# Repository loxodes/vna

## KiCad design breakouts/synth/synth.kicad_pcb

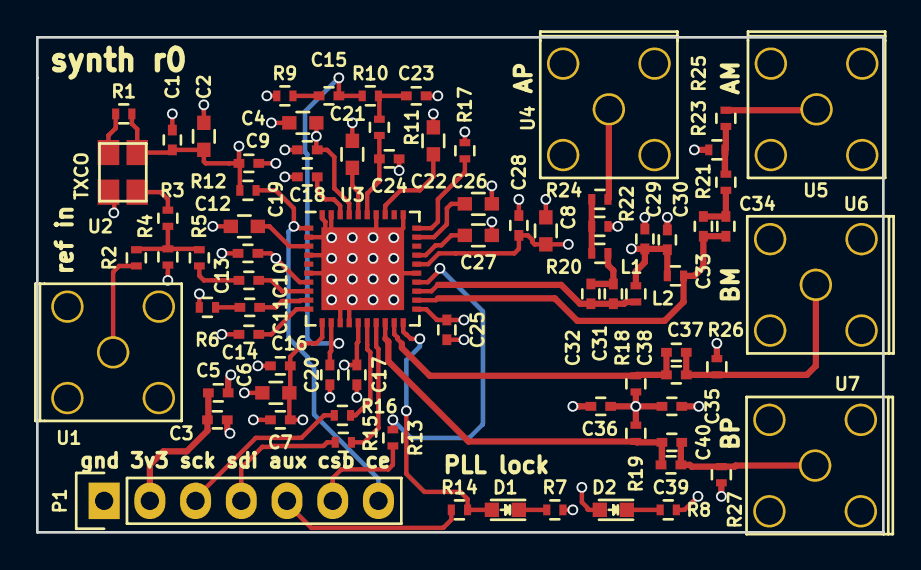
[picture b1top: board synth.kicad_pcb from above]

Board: 4 copper layers, 47.0 x 27.5 mm, 80 parts (0 on the bottom side), 45 nets.

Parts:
C1, C3, C5, C7, C9, C10, C11, C13, C16, C18, C20, C25, C28, C30, C32, C34, C36, C38, C40: 100 nF; C_0402
C2, C4, C6, C8, C12, C21, C22, C26, C27: 10 uF; C_0603
C14, C19: 1 uF; C_0402
C15: 47 nF; C_0402
C17: 560 pF; C_0402
C23: DNP; C_0402
C24: 6800 pF; C_0402
C29, C31, C33, C35, C37, C39: 30 pF; C_0402
D1, D2: LED; LED_0603
L1, L2: 18 nF; R_0402
P1: CONN_01X07; Pin_Header_Straight_1x07
R1: R_Small; R_0402
R2, R4: DNP; R_0402
R3, R5, R11: 0; R_0402
R6, R7, R8, R12, R13, R14, R15, R16: 1k; R_0402
R9: 150; R_0402
R10: 12; R_0402
R17: 680; R_0402
R18, R19, R20, R21, R22, R23, R24, R25, R26, R27: 49.9; R_0402
U1, U4, U5, U6, U7: CONN_SMA; 732512200_SMA
U2: TXCO; crystal_FA238-TSX3225
U3: LMX2592; QFN-40-1EP_6x6mm_Pitch0.5mm
U8: mounting_box; POMONA_2400BOX

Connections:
/CE: P1.7, R12.2, U3.1
/CSB: R13.1, U3.24
/MUXout: D1.2, R14.1, U3.20
/RFoutAM: C33.2, C34.2, L2.2, U3.22
/RFoutAP: C31.2, C32.2, L1.1, U3.23
/RFoutBM: C37.2, C38.2, R18.2, U3.19
/RFoutBP: C39.2, C40.2, R19.1, U3.18
/SCK: R16.1, U3.16
/SDI: R15.1, U3.17
/Vtune_mid: C15.1, C17.1, R10.1, U3.12
GND: C1.2, C2.2, C3.2, C4.2, C5.2, C6.2, C7.2, C8.2, C9.2, C12.2, C13.1, C14.1, C16.1, C17.2, C18.2, C19.1, C20.1, C21.2, C22.2, C23.1, C24.1, C25.2, C26.2, C27.2, C28.1, C29.1, C30.1, C35.1, C36.1, P1.1, R4.2, R6.2, R7.1, R8.1, R9.1, R17.1, R22.1, R23.1, R26.1, R27.1, U1.2, U1.3, U1.4, U1.5, U2.2, U3.2, U3.4, U3.6, U3.13, U3.14, U3.25, U3.31, U3.34, U3.39, U3.40, U3.41, U4.2, U4.3, U4.4, U4.5, U5.2, U5.3, U5.4, U5.5, U6.2, U6.3, U6.4, U6.5, U7.2, U7.3, U7.4, U7.5
unnamed: C10.1, U3.8
unnamed: C10.2, R5.1
unnamed: C11.1, R6.1
unnamed: C11.2, U3.9
unnamed: C12.1, U3.3
unnamed: C14.2, U3.10
unnamed: C15.2, R9.2
unnamed: C19.2, U3.38
unnamed: C21.1, U3.36
unnamed: C22.1, U3.33
unnamed: C23.2, R10.2, R11.1
unnamed: C24.2, R11.2, U3.35
unnamed: C26.1, U3.29
unnamed: C27.1, U3.27
unnamed: C31.1, C32.1, R20.1
unnamed: C33.1, C34.1, R21.1
unnamed: C37.1, C38.1, R26.2, U6.1
unnamed: C39.1, C40.1, R27.2, U7.1
unnamed: D1.1, R7.2
unnamed: D2.1, R8.2
unnamed: P1.3, R16.2
unnamed: P1.4, R15.2
unnamed: P1.5, R14.2
unnamed: P1.6, R13.2
unnamed: R1.1, U2.1
unnamed: R2.1, U1.1
unnamed: R2.2, R3.2, R4.1, R5.2
unnamed: R3.1, U2.3
unnamed: R17.2, U3.30
unnamed: R20.2, R22.2, R24.1
unnamed: R21.2, R23.2, R25.1
unnamed: R24.2, U4.1
unnamed: R25.2, U5.1
VCC: C1.1, C2.1, C3.1, C4.1, C5.1, C6.1, C7.1, C8.1, C9.1, C13.2, C16.2, C18.1, C20.2, C25.1, C28.2, C29.2, C30.2, C35.2, C36.2, D2.2, L1.2, L2.1, P1.2, R1.2, R12.1, R18.1, R19.2, U2.4, U3.7, U3.11, U3.15, U3.21, U3.26, U3.37

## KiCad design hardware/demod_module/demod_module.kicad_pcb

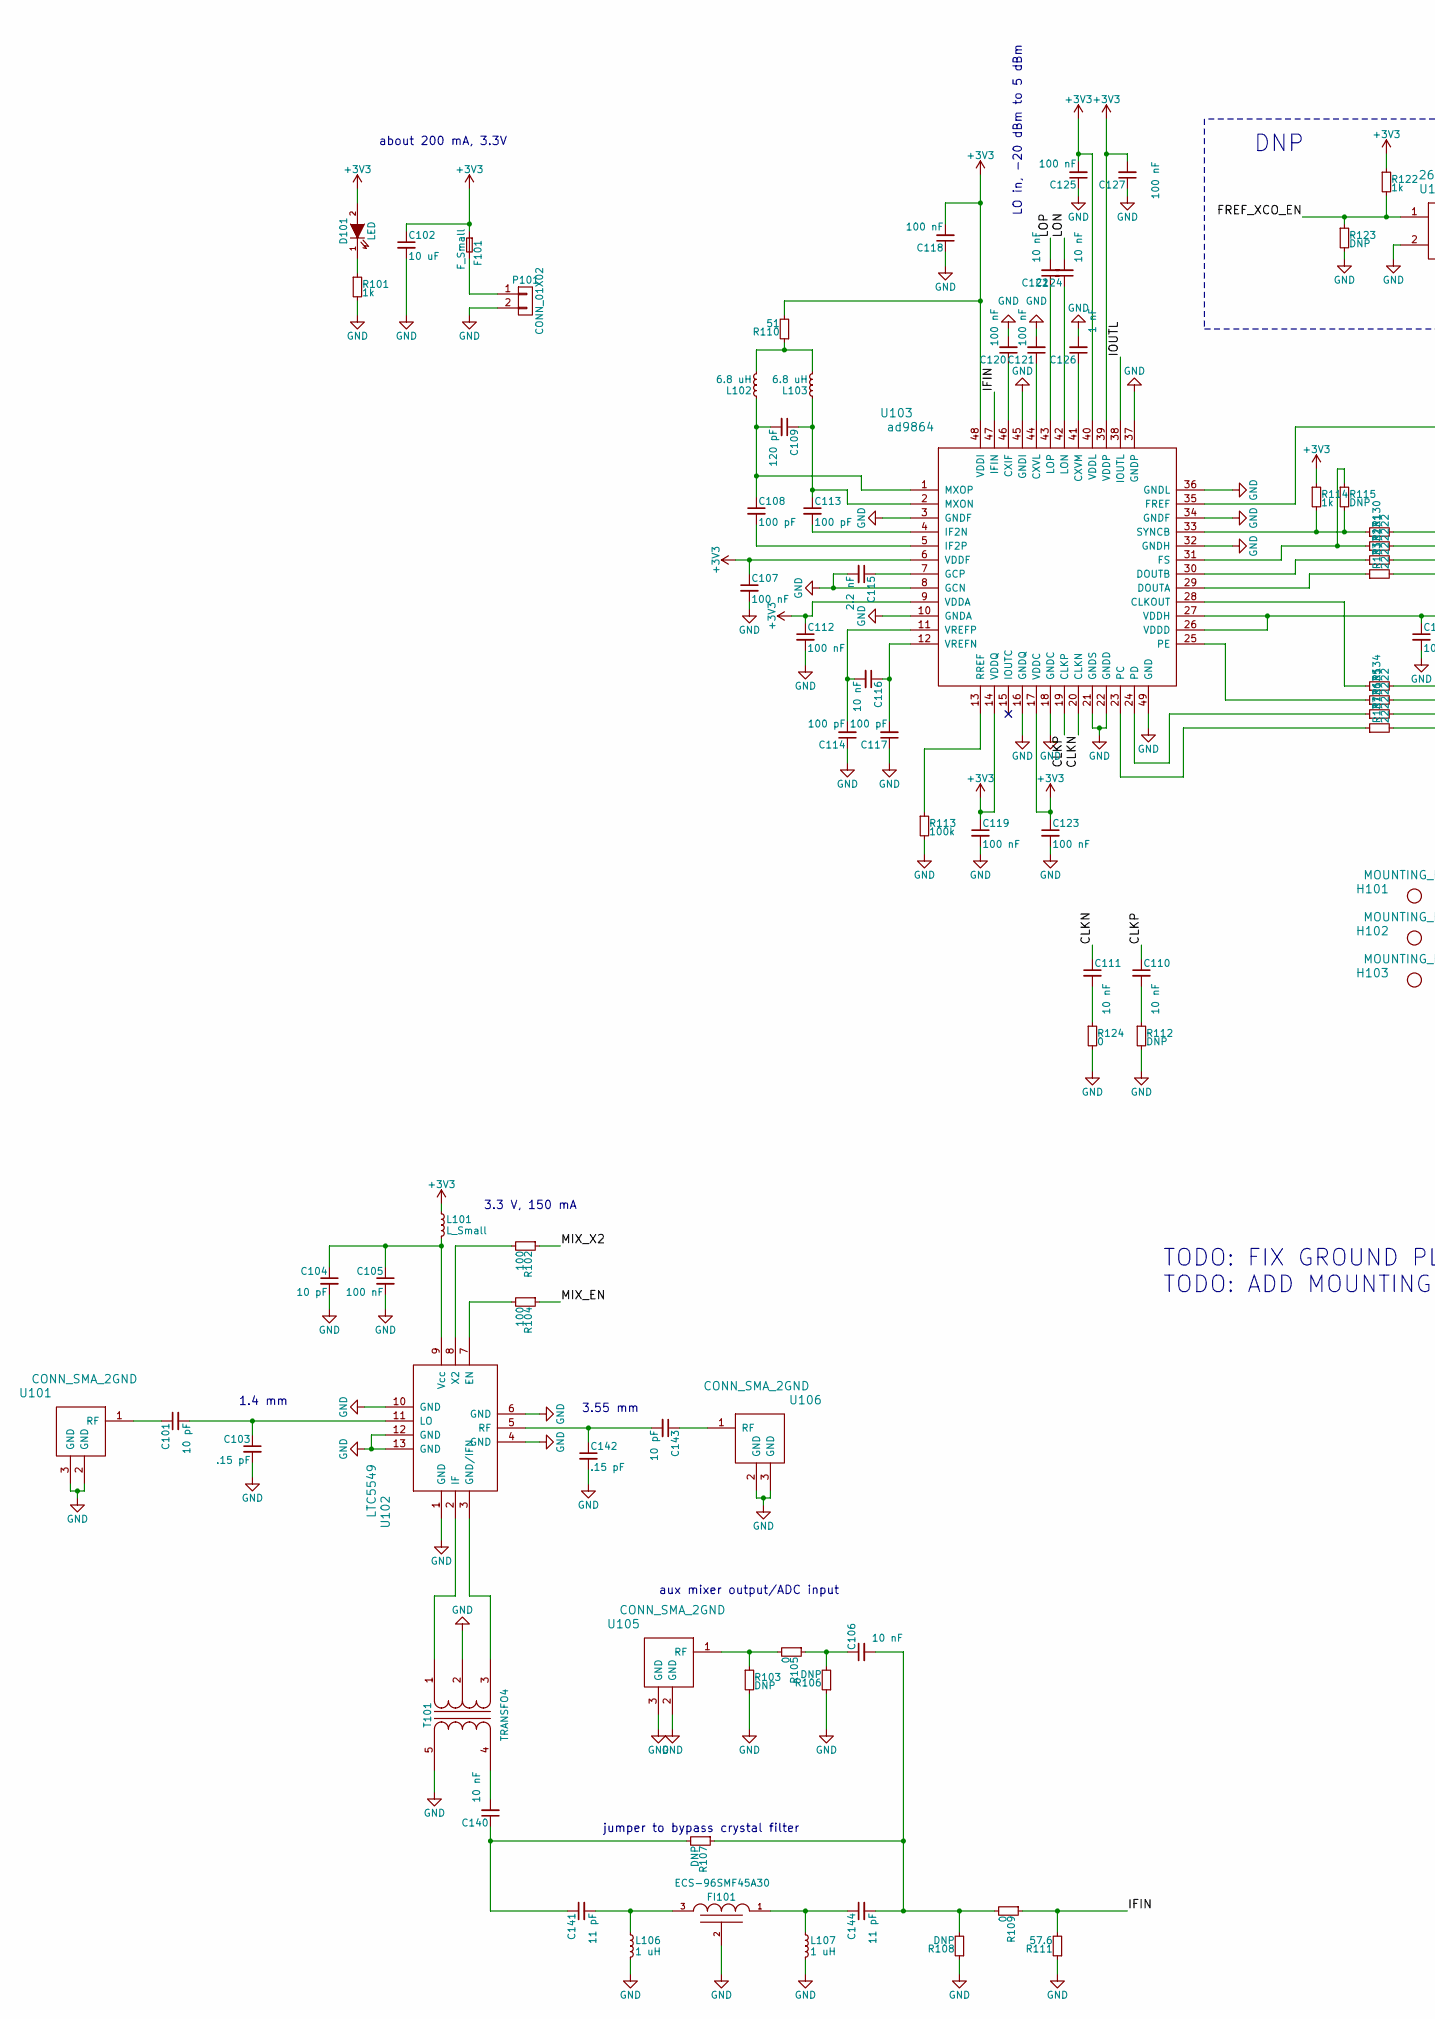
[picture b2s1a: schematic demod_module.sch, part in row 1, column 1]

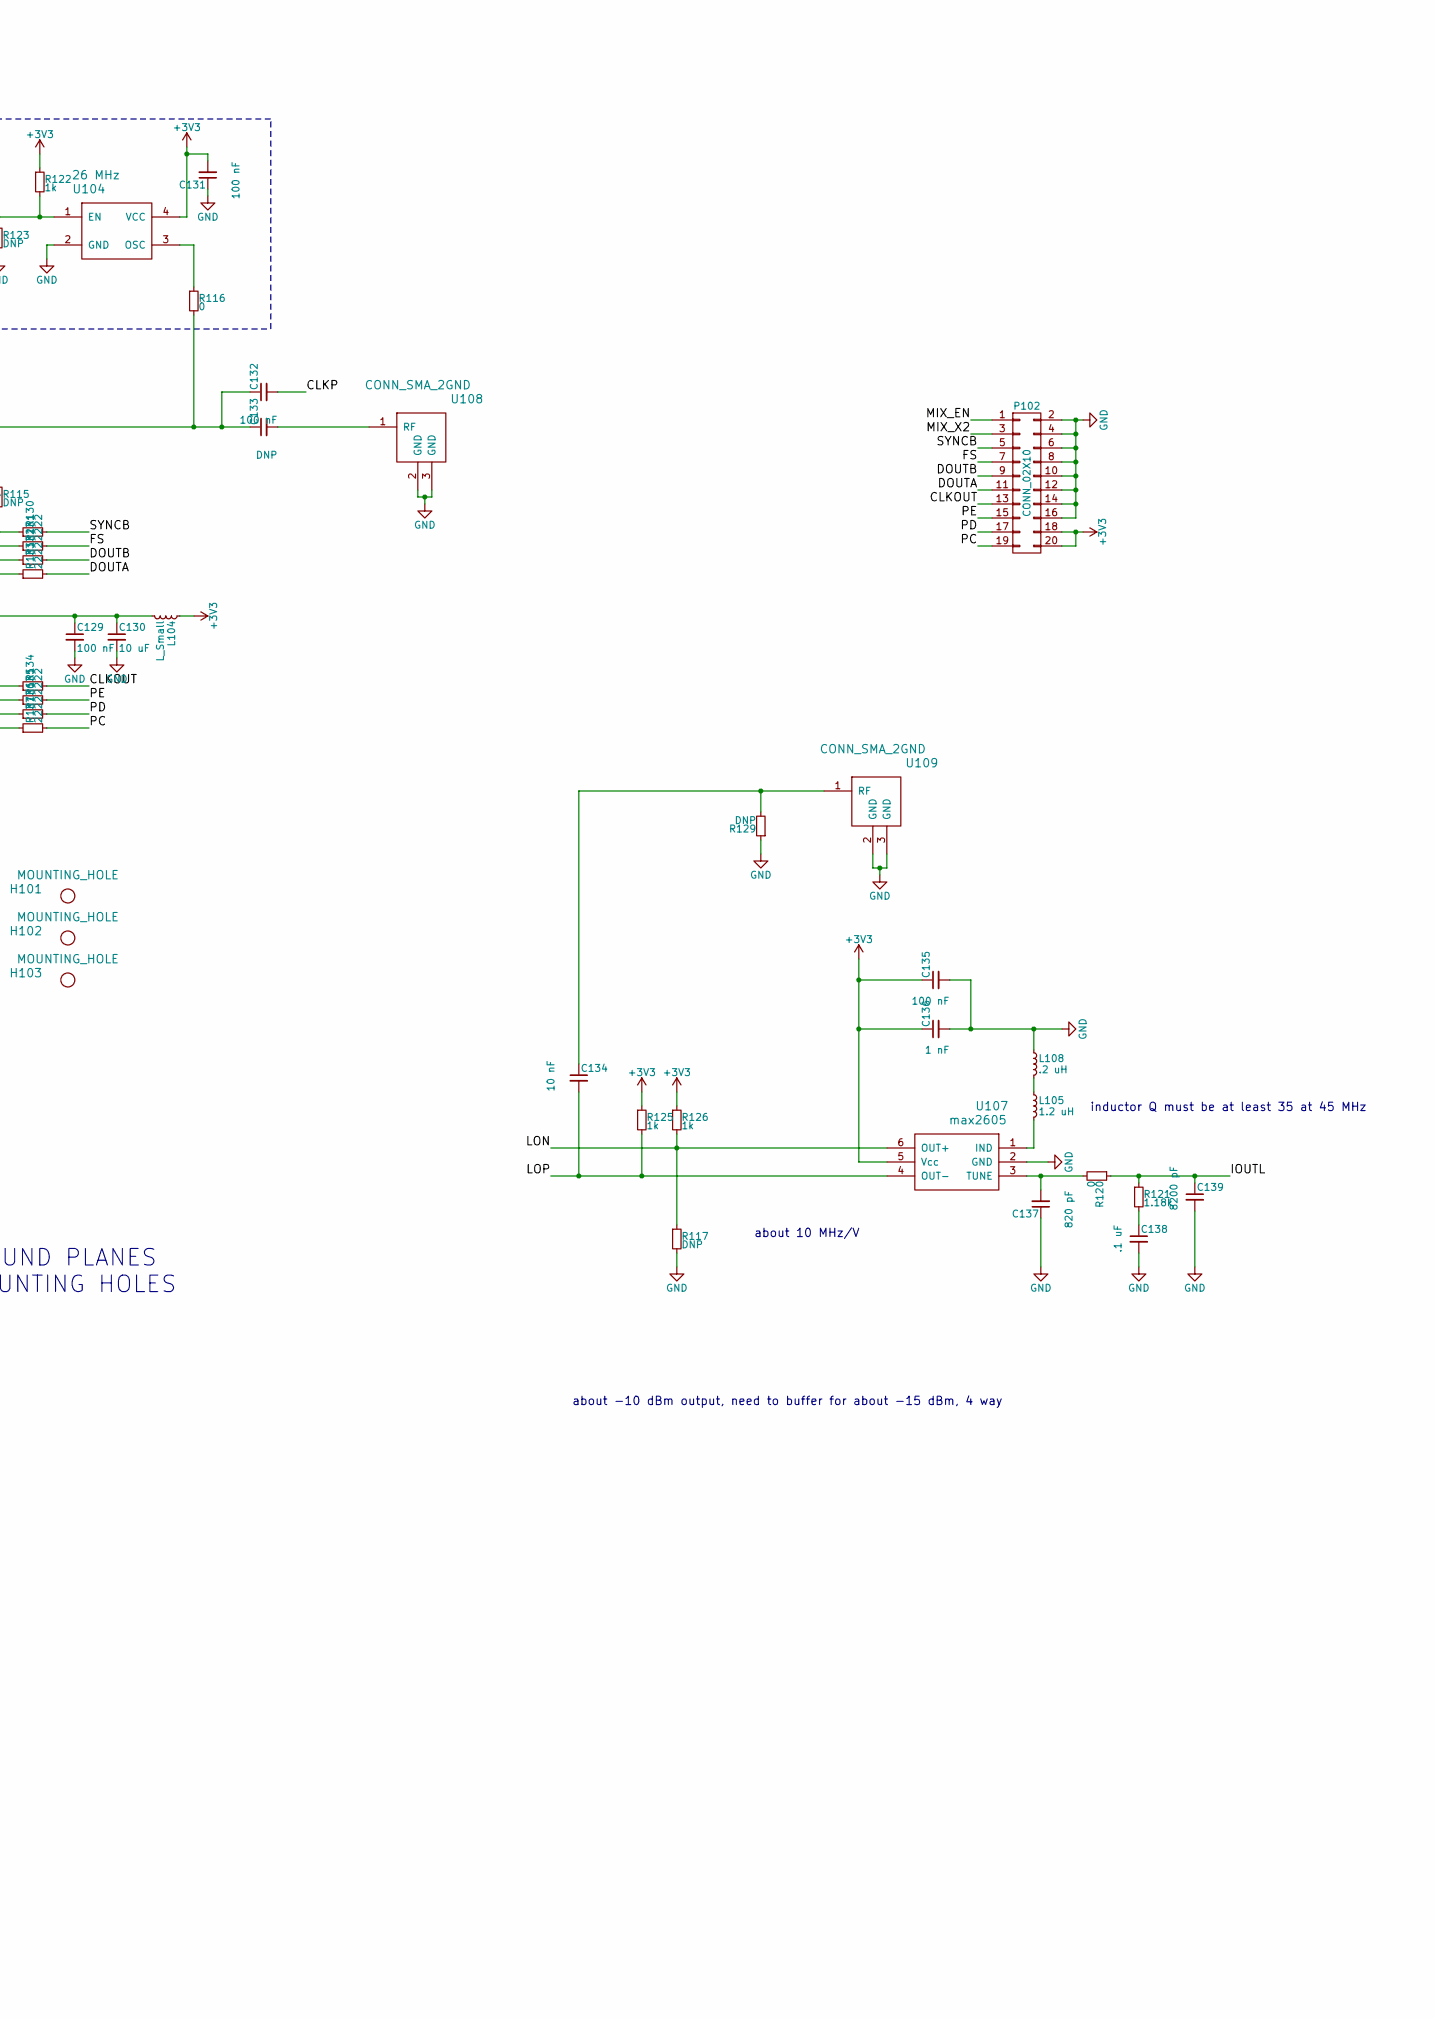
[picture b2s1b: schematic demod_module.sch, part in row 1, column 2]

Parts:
C101, C104, C143: 10 pF; C_0402
C102, C130: 10 uF; C_0603
C103, C142: .15 pF; C_0402
C105, C107, C112, C118, C119, C120, C121, C123, C125, C127, C129, C131, C132, C135: 100 nF; C_0402
C106, C110, C111, C116, C122, C124, C134, C140: 10 nF; C_0402
C108, C113, C114, C117: 100 pF; C_0402
C109: 120 pF; C_0402
C115: 2.2 nF; C_0402
C126, C136: 1 nF; C_0402
C133: DNP; C_0402
C137: 820 pF; C_0402
C138: .1 uF; C_0402
C139: 8200 pF; C_0402
C141, C144: 11 pF; C_0402
D101: LED; LED_0603
F101: F_Small; R_1812
FI101: ECS-96SMF45A30; ECS-96SMF
H101, H102, H103: MOUNTING_HOLE; MountingHole_2-7mm
L101, L104: L_Small; R_0402
L102, L103: 6.8 uH; R_0805
L105: 1.2 uH; R_0805
L106, L107: 1 uH; R_0805
L108: .2 uH; R_0805
P101: CONN_01X02; TerminalBlock_Pheonix_PT-3.5mm_2pol
P102: CONN_02X10; Pin_Header_Straight_2x10
R101, R114, R122, R125, R126: 1k; R_0402
R102, R104: 100; R_0402
R103, R106, R107, R108, R112, R115, R117, R123, R129: DNP; R_0402
R105, R109, R116, R120, R124: 0; R_0402
R110: 51; R_0402
R111: 57.6; R_0402
R113: 100k; R_0402
R121: 1.18k; R_0402
R130, R131, R132, R133, R134, R135, R136, R137: 22; R_0402
T101: TRANSFO4; 5LEAD_BALUN_4p83mm_3p3mm
U101, U106: CONN_SMA_2GND; SMA_CPW_1MM_.2MM
U102: LTC5549; QFN_12_3mm2mm
U103: ad9864; QFN-48-1EP_7x7mm_Pitch0.5mm
U104: 26 MHz; crystal_FA238-TSX3225
U105, U108, U109: CONN_SMA_2GND; 734120110_ufl_umc
U107: max2605; SOT-23-6

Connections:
+3V3: C102.1, C107.1, C112.1, C118.2, C119.1, C123.1, C125.2, C127.2, C131.2, C135.1, C136.1, D101.2 (A), F101.1, L101.1, L104.1, P102.18, P102.20, R110.2, R114.1, R122.1, R125.1, R126.1, U103.6 (VDDF), U103.9 (VDDA), U103.14 (VDDQ), U103.17 (VDDC), U103.39 (VDDP), U103.40 (VDDL), U103.48 (VDDI), U104.4 (VCC), U107.5 (Vcc)
/CLKN: C111.1, U103.20 (CLKN)
/CLKOUT: P102.13, R134.2
/CLKP: C110.1, C132.2, U103.19 (CLKP)
/DOUTA: P102.11, R133.2
/DOUTB: P102.9, R132.2
/FREF_XCO_EN: R122.2, R123.1, U104.1 (EN)
/FS: P102.7, R131.2
/IFIN: R109.1, R111.2, U103.47 (IFIN)
/IOUTL: C139.1, R120.1, R121.1, U103.38 (IOUTL)
/LON: C124.2, R117.1, R126.2, U107.6 (OUT+)
/LOP: C122.2, C134.2, R125.2, U107.4 (OUT-)
/MIX_EN: P102.1, R104.1
/MIX_X2: P102.3, R102.1
/PC: P102.19, R137.2
/PD: P102.17, R136.2
/PE: P102.15, R135.2
/SYNCB: P102.5, R130.2
GND: C102.2, C103.2, C104.2, C105.2, C107.2, C112.2, C114.1, C115.2, C117.1, C118.1, C119.2, C120.2, C121.2, C123.2, C125.1, C126.2, C127.1, C129.2, C130.2, C131.1, C135.2, C136.2, C137.1, C138.2, C139.2, C142.2, FI101.2 (GND), L106.2, L107.2, L108.1, P101.2, P102.2, P102.4, P102.6, P102.8, P102.10, P102.12, P102.14, P102.16, R101.2, R103.2, R106.1, R108.1, R111.1, R112.2, R113.2, R117.2, R123.2, R124.2, R129.1, T101.2 (PM), T101.5 (S2), U101.2 (GND), U101.3 (GND), U102.1 (GND), U102.4 (GND), U102.6 (GND), U102.10 (GND), U102.12 (GND), U102.13 (GND), U103.3 (GNDF), U103.8 (GCN), U103.10 (GNDA), U103.16 (GNDQ), U103.18 (GNDC), U103.21 (GNDS), U103.22 (GNDD), U103.32 (GNDH), U103.34 (GNDF), U103.36 (GNDL), U103.37 (GNDP), U103.45 (GNDI), U103.49 (GND), U104.2 (GND), U105.2 (GND), U105.3 (GND), U106.2 (GND), U106.3 (GND), U107.2 (GND), U108.2 (GND), U108.3 (GND), U109.2 (GND), U109.3 (GND)
unnamed: C101.1, U101.1 (RF)
unnamed: C101.2, C103.1, U102.11 (LO)
unnamed: C104.1, C105.1, L101.2, U102.9 (Vcc)
unnamed: C106.1, R105.1, R106.2
unnamed: C106.2, C144.2, R107.1, R108.2, R109.2
unnamed: C108.1, C109.2, L102.1, U103.1 (MXOP)
unnamed: C108.2, U103.5 (IF2P)
unnamed: C109.1, C113.1, L103.1, U103.2 (MXON)
unnamed: C110.2, R112.1
unnamed: C111.2, R124.1
unnamed: C113.2, U103.4 (IF2N)
unnamed: C114.2, C116.2, U103.11 (VREFP)
unnamed: C115.1, U103.7 (GCP)
unnamed: C116.1, C117.2, U103.12 (VREFN)
unnamed: C120.1, U103.46 (CXIF)
unnamed: C121.1, U103.44 (CXVL)
unnamed: C122.1, U103.43 (LOP)
unnamed: C124.1, U103.42 (LON)
unnamed: C126.1, U103.41 (CXVM)
unnamed: C129.1, C130.1, L104.2, U103.26 (VDDD), U103.27 (VDDH)
unnamed: C132.1, C133.1, R116.2, U103.35 (FREF)
unnamed: C133.2, U108.1 (RF)
unnamed: C134.1, R129.2, U109.1 (RF)
unnamed: C137.2, R120.2, U107.3 (TUNE)
unnamed: C138.1, R121.2
unnamed: C140.1, C141.1, R107.2
unnamed: C140.2, T101.4 (S1)
unnamed: C141.2, FI101.3 (VO), L106.1
unnamed: C142.1, C143.2, U102.5 (RF)
unnamed: C143.1, U106.1 (RF)
unnamed: C144.1, FI101.1 (VI), L107.1
unnamed: D101.1 (K), R101.1
unnamed: F101.2, P101.1
unnamed: L102.2, L103.2, R110.1
unnamed: L105.1, L108.2
unnamed: L105.2, U107.1 (IND)
unnamed: R102.2, U102.8 (X2)
unnamed: R103.1, R105.2, U105.1 (RF)
unnamed: R104.2, U102.7 (EN)
unnamed: R113.1, U103.13 (RREF)
unnamed: R114.2, R115.2, R130.1, U103.33 (SYNCB)
unnamed: R115.1, R131.1, U103.31 (FS)
unnamed: R116.1, U104.3 (OSC)
unnamed: R132.1, U103.30 (DOUTB)
unnamed: R133.1, U103.29 (DOUTA)
unnamed: R134.1, U103.28 (CLKOUT)
unnamed: R135.1, U103.25 (PE)
unnamed: R136.1, U103.24 (PD)
unnamed: R137.1, U103.23 (PC)
unnamed: T101.1 (PR1), U102.2 (IF)
unnamed: T101.3 (PR2), U102.3 (GND/IFN)

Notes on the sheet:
about 10 MHz/V
inductor Q must be at least 35 at 45 MHz
DNP
3.3 V, 150 mA
LO in, -20 dBm to 5 dBm
about -10 dBm output, need to buffer for about -15 dBm, 4 way
jumper to bypass crystal filter
aux mixer output/ADC input
about 200 mA, 3.3V
TODO: FIX GROUND PLANES TODO: ADD MOUNTING HOLES
3.55 mm
1.4 mm

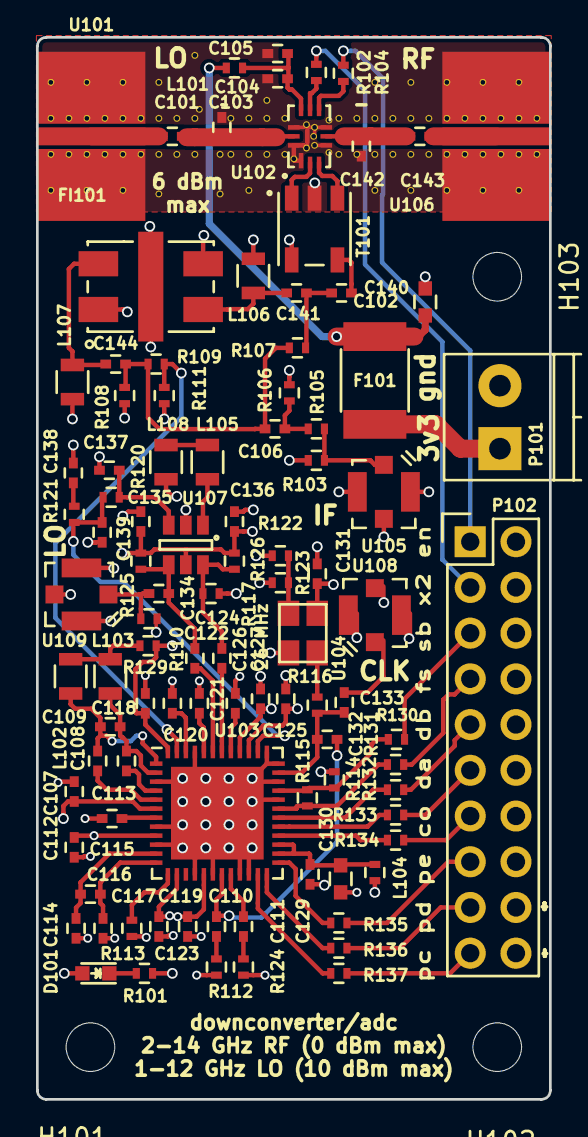
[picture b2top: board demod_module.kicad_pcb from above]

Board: 4 copper layers, 28.5 x 59.0 mm, 102 parts (0 on the bottom side), 70 nets.

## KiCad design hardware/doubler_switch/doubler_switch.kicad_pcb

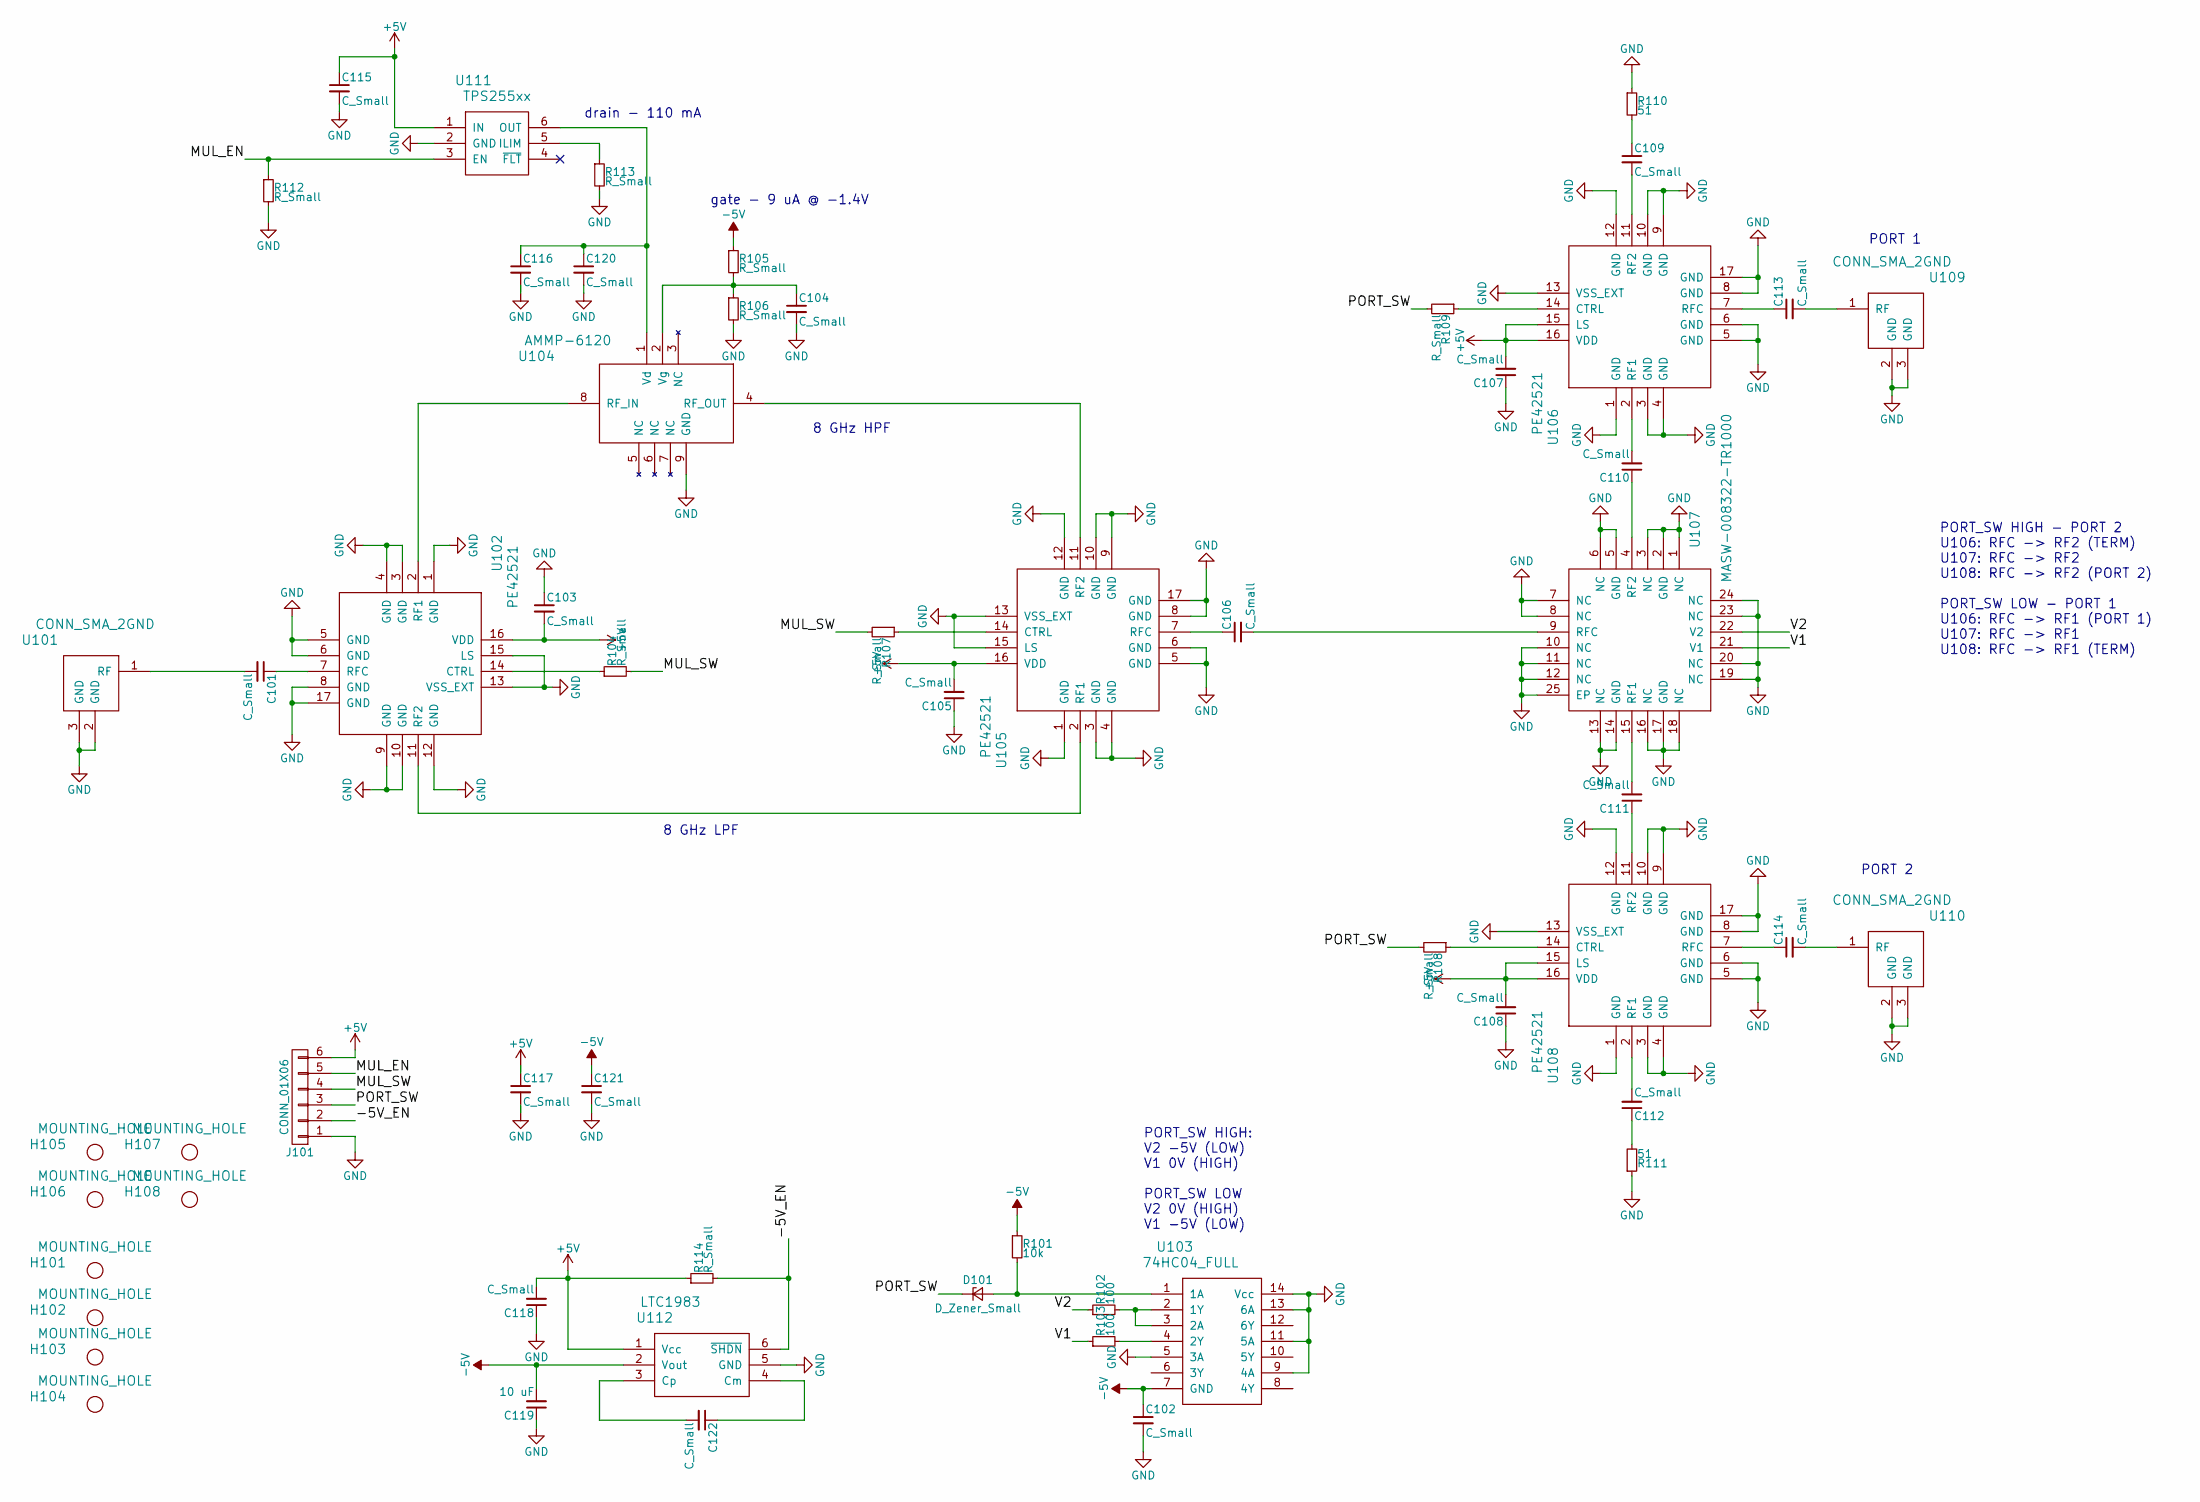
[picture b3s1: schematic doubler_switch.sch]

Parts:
C101, C102, C103, C104, C105, C106, C107, C108, C109, C110, C111, C112, C113, C114, C115, C116: C_Small; C_0402
C117, C118, C120, C121, C122: C_Small; C_0603
C119: 10 uF; C_0603
D101: D_Zener_Small; SOD-323
H101, H102, H103, H104: MOUNTING_HOLE; MountingHole_3mm
H105, H106, H107, H108: MOUNTING_HOLE; MountingHole_2-5mm
J101: CONN_01X06; Pin_Header_Straight_1x06
R101: 10k; R_0402
R102, R103: 100; R_0402
R104, R105, R106, R107, R108, R109, R112, R113, R114: R_Small; R_0402
R110, R111: 51; R_0402
U101, U109, U110: CONN_SMA_2GND; SMA_901-10512_30MIL_OSHFR408_CPW_LAUNCH
U102, U105, U106, U108: PE42521; QFN-16-1EP_3x3mm_Pitch0.5mm
U103: 74HC04_FULL; TSSOP-14_4.4x5mm_Pitch0.65mm
U104: AMMP-6120; 8QFN_5mm
U107: MASW-008322-TR1000; QFN-24-1EP_4x4mm_Pitch0.5mm
U111: TPS255xx; SOT-23-6
U112: LTC1983; SOT-23-6

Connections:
+5V: C103.2, C105.2, C107.2, C108.2, C115.1, C117.1, C118.2, J101.6, R114.1, U102.16 (VDD), U105.16 (VDD), U106.15 (LS), U106.16 (VDD), U108.15 (LS), U108.16 (VDD), U111.1 (IN), U112.1 (Vcc)
-5V: C102.1, C119.2, C121.1, R101.1, R105.1, U103.7 (GND), U112.2 (Vout)
/-5V_EN: J101.2, R114.2, U112.6 (~SHDN)
/MUL_EN: J101.5, R112.1, U111.3 (EN)
/MUL_SW: J101.4, R104.2, R107.2
/PORT_SW: D101.1 (K), J101.3, R108.2, R109.2
/V1: R103.1, U107.21 (V1)
/V2: R102.1, U107.22 (V2)
GND: C102.2, C103.1, C104.2, C105.1, C107.1, C108.1, C115.2, C116.2, C117.2, C118.1, C119.1, C120.2, C121.2, J101.1, R106.2, R110.1, R111.1, R112.2, R113.2, U101.2 (GND), U101.3 (GND), U102.1 (GND), U102.3 (GND), U102.4 (GND), U102.5 (GND), U102.6 (GND), U102.8 (GND), U102.9 (GND), U102.10 (GND), U102.12 (GND), U102.13 (VSS_EXT), U102.15 (LS), U102.17 (GND), U103.5 (3A), U103.9 (4A), U103.11 (5A), U103.13 (6A), U103.14 (Vcc), U104.9 (GND), U105.1 (GND), U105.3 (GND), U105.4 (GND), U105.5 (GND), U105.6 (GND), U105.8 (GND), U105.9 (GND), U105.10 (GND), U105.12 (GND), U105.13 (VSS_EXT), U105.15 (LS), U105.17 (GND), U106.1 (GND), U106.3 (GND), U106.4 (GND), U106.5 (GND), U106.6 (GND), U106.8 (GND), U106.9 (GND), U106.10 (GND), U106.12 (GND), U106.13 (VSS_EXT), U106.17 (GND), U107.1 (NC), U107.2 (GND), U107.3 (NC), U107.5 (GND), U107.6 (NC), U107.7 (NC), U107.8 (NC), U107.10 (NC), U107.11 (NC), U107.12 (NC), U107.13 (NC), U107.14 (GND), U107.16 (NC), U107.17 (GND), U107.18 (NC), U107.19 (NC), U107.20 (NC), U107.23 (NC), U107.24 (NC), U107.25 (EP), U108.1 (GND), U108.3 (GND), U108.4 (GND), U108.5 (GND), U108.6 (GND), U108.8 (GND), U108.9 (GND), U108.10 (GND), U108.12 (GND), U108.13 (VSS_EXT), U108.17 (GND), U109.2 (GND), U109.3 (GND), U110.2 (GND), U110.3 (GND), U111.2 (GND), U112.5 (GND)
unnamed: C101.1, U102.7 (RFC)
unnamed: C101.2, U101.1 (RF)
unnamed: C104.1, R105.2, R106.1, U104.2 (Vg)
unnamed: C106.1, U105.7 (RFC)
unnamed: C106.2, U107.9 (RFC)
unnamed: C109.1, R110.2
unnamed: C109.2, U106.11 (RF2)
unnamed: C110.1, U107.4 (RF2)
unnamed: C110.2, U106.2 (RF1)
unnamed: C111.1, U108.11 (RF2)
unnamed: C111.2, U107.15 (RF1)
unnamed: C112.1, R111.2
unnamed: C112.2, U108.2 (RF1)
unnamed: C113.1, U106.7 (RFC)
unnamed: C113.2, U109.1 (RF)
unnamed: C114.1, U108.7 (RFC)
unnamed: C114.2, U110.1 (RF)
unnamed: C116.1, C120.1, U104.1 (Vd), U111.6 (OUT)
unnamed: C122.1, U112.4 (Cm)
unnamed: C122.2, U112.3 (Cp)
unnamed: D101.2 (A), R101.2, U103.1 (1A)
unnamed: R102.2, U103.2 (1Y), U103.3 (2A)
unnamed: R103.2, U103.4 (2Y)
unnamed: R104.1, U102.14 (CTRL)
unnamed: R107.1, U105.14 (CTRL)
unnamed: R108.1, U108.14 (CTRL)
unnamed: R109.1, U106.14 (CTRL)
unnamed: R113.1, U111.5 (ILIM)
unnamed: U102.2 (RF1), U104.8 (RF_IN)
unnamed: U102.11 (RF2), U105.2 (RF1)
unnamed: U104.4 (RF_OUT), U105.11 (RF2)

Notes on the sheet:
PORT_SW HIGH - PORT 2 U106: RFC -> RF2 (TERM) U107: RFC -> RF2 U108: RFC -> RF2 (PORT 2) PORT_SW LOW - PORT 1 U106: RFC -> RF1 (PORT 1) U107: RFC -> RF1 U108: RFC -> RF1 (TERM)
PORT_SW HIGH: V2 -5V (LOW) V1 0V (HIGH) PORT_SW LOW V2 0V (HIGH) V1 -5V (LOW)
PORT 2
PORT 1
gate - 9 uA @ -1.4V
drain - 110 mA
8 GHz LPF
8 GHz HPF

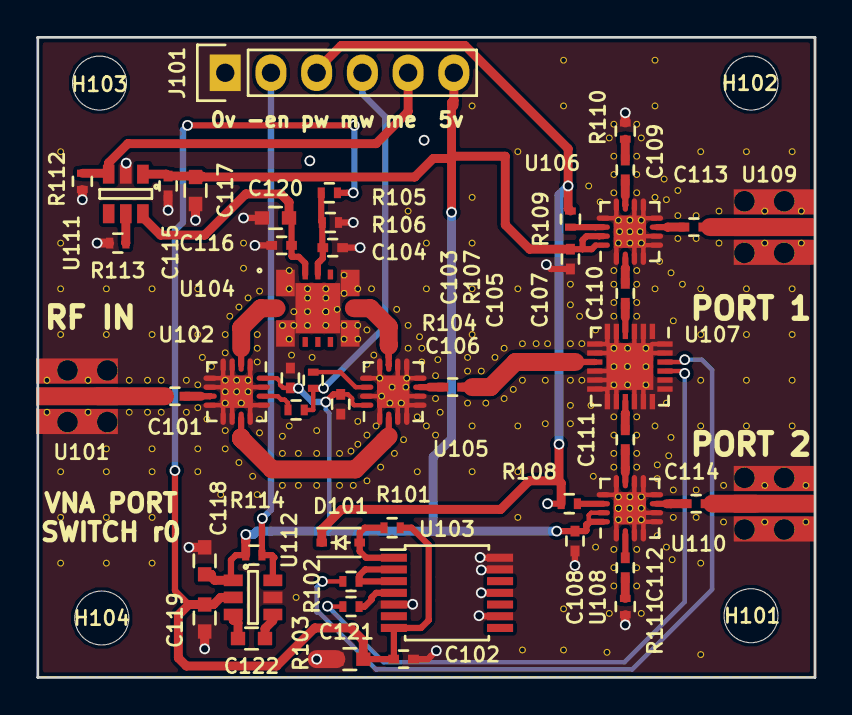
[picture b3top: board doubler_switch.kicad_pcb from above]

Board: 4 copper layers, 43.2 x 35.6 mm, 54 parts (0 on the bottom side), 40 nets.

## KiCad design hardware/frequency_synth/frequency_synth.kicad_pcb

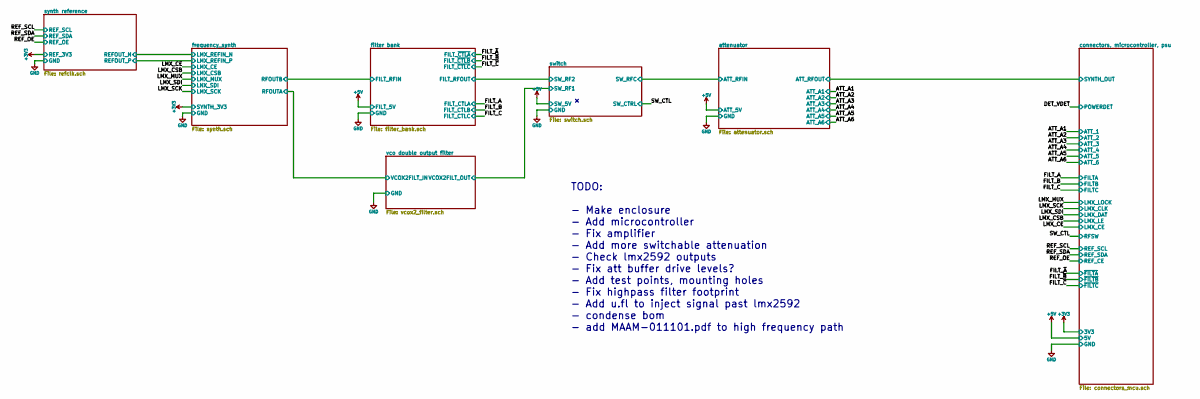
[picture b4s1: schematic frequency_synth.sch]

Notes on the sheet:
TODO: - Make enclosure - Add microcontroller - Fix amplifier - Add more switchable attenuation - Check lmx2592 outputs - Fix att buffer drive levels? - Add test points, mounting holes - Fix highpass filter footprint - Add u.fl to inject signal past lmx2592 - condense bom - add MAAM-011101.pdf to hi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
